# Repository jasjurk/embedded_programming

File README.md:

# embedded_programming
Some small projects for my electronics hobby.

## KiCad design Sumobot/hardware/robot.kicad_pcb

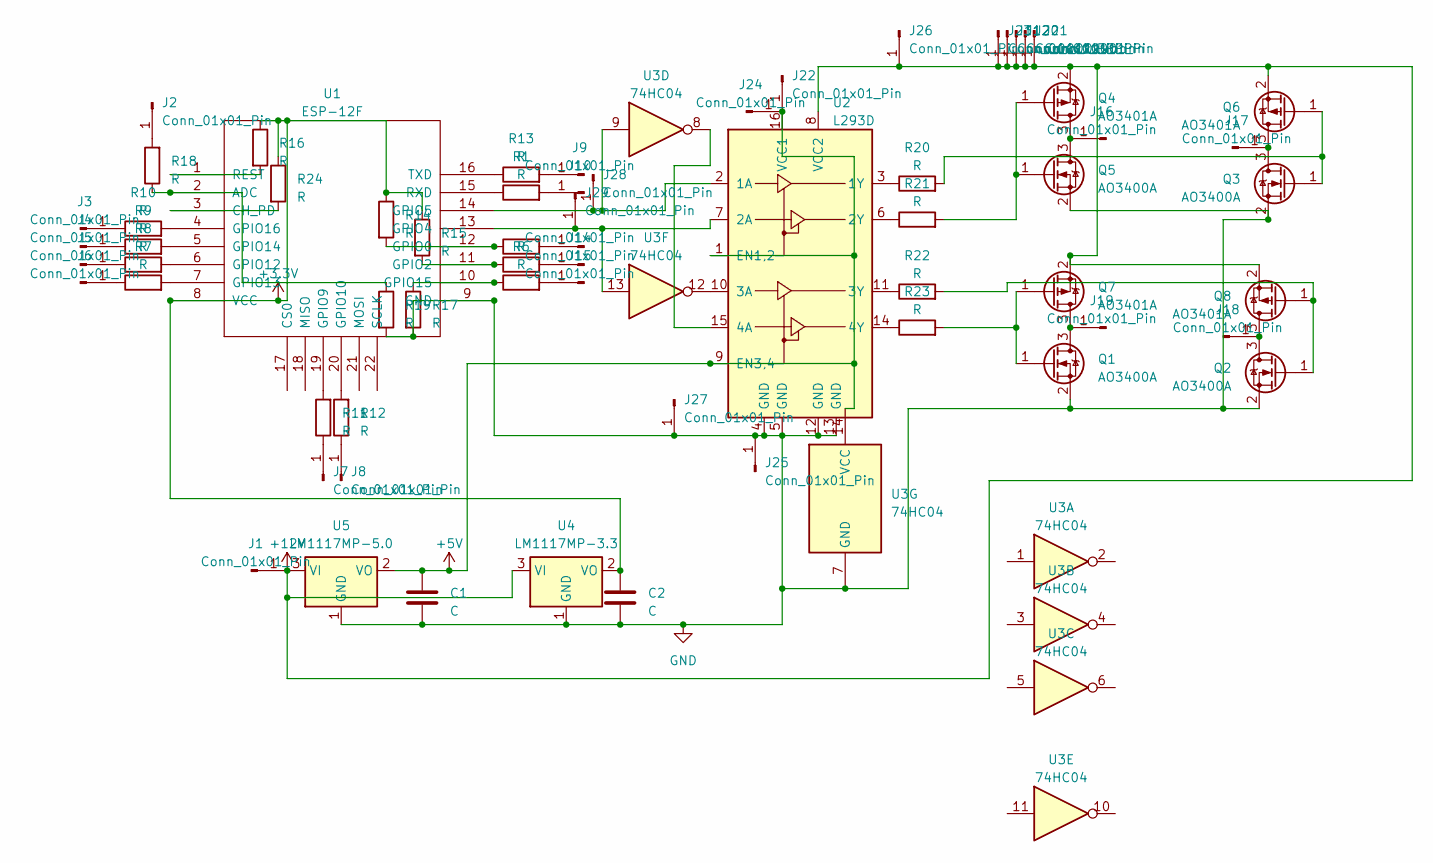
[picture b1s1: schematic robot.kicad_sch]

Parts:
C1, C2: C; C_1206_3216Metric_Pad1.33x1.80mm_HandSolder
J1, J2, J3, J4, J5, J6, J7, J8, J9, J10, J13, J14, J15, J16, J17, J18, J19, J25: Conn_01x01_Pin; SolderWirePad_1x01_SMD_1x2mm
J11, J12, J20, J21, J22, J23, J24, J26, J27, J28, J29: Conn_01x01_Pin; PinHeader_1x01_P1.00mm_Vertical
Q1, Q2, Q3, Q5: AO3400A; SOT-23
Q4, Q6, Q7, Q8: AO3401A; SOT-23
R1, R4, R5, R6, R7, R8, R9, R10, R11, R12, R13, R14, R15, R16, R17, R18, R19, R20, R21, R22, R23, R24: R; R_0805_2012Metric_Pad1.20x1.40mm_HandSolder
U1: ESP-12F; ESP-12E_SMD
U2: L293D; DIP-16_W7.62mm
U3: 74HC04; DIP-14_W7.62mm
U4: LM1117MP-3.3; SOT-223-3_TabPin2
U5: LM1117MP-5.0; SOT-223-3_TabPin2

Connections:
+3.3V: C2.1, R14.1, R15.1, R16.1, R24.1, U1.8 (VCC), U4.2 (VO)
+5V: C1.1, J22.1, J24.1, U2.1 (EN1,2), U2.9 (EN3,4), U2.16 (VCC1), U3.14 (VCC), U5.2 (VO)
+12V: J1.1, J11.1, J12.1, J20.1, J21.1, J23.1, J26.1, Q4.2 (S), Q6.2 (S), Q7.2 (S), Q8.2 (S), U2.8 (VCC2), U4.3 (VI), U5.3 (VI)
GND: C1.2, C2.2, J25.1, J27.1, Q1.2 (S), Q2.2 (S), Q3.2 (S), Q5.2 (S), R17.2, R19.2, U1.9 (GND), U2.4 (GND), U2.5 (GND), U2.12 (GND), U2.13 (GND), U3.7 (GND), U4.1 (GND), U5.1 (GND)
unnamed: J2.1, R18.2
unnamed: J3.1, R10.1
unnamed: J4.1, R9.1
unnamed: J5.1, R8.1
unnamed: J6.1, R7.1
unnamed: J7.1, R11.1
unnamed: J8.1, R12.1
unnamed: J9.1, R13.2
unnamed: J10.1, R1.2
unnamed: J13.1, R4.2
unnamed: J14.1, R5.2
unnamed: J15.1, R6.2
unnamed: J16.1, Q4.3 (D), Q5.3 (D)
unnamed: J17.1, Q3.3 (D), Q6.3 (D)
unnamed: J18.1, Q2.3 (D), Q8.3 (D)
unnamed: J19.1, Q1.3 (D), Q7.3 (D)
unnamed: J28.1, U1.14 (GPIO5), U2.2 (1A), U3.9
unnamed: J29.1, U1.13 (GPIO4), U2.7 (2A), U3.13
unnamed: Q1.1 (G), Q7.1 (G), R23.2
unnamed: Q2.1 (G), Q8.1 (G), R22.2
unnamed: Q3.1 (G), Q6.1 (G), R20.2
unnamed: Q4.1 (G), Q5.1 (G), R21.2
unnamed: R18.1, R19.1, U1.2 (ADC)
unnamed: R24.2, U1.3 (CH_PD)
unnamed: R4.1, R14.2, U1.12 (GPIO0)
unnamed: R5.1, R15.2, U1.11 (GPIO2)
unnamed: R11.2, U1.19 (GPIO9)
unnamed: R12.2, U1.20 (GPIO10)
unnamed: R8.2, U1.6 (GPIO12)
unnamed: R7.2, U1.7 (GPIO13)
unnamed: R9.2, U1.5 (GPIO14)
unnamed: R6.1, R17.1, U1.10 (GPIO15)
unnamed: R10.2, U1.4 (GPIO16)
unnamed: R16.2, U1.1 (REST)
unnamed: R1.1, U1.15 (RXD)
unnamed: R13.1, U1.16 (TXD)
unnamed: R20.1, U2.3 (1Y)
unnamed: R21.1, U2.6 (2Y)
unnamed: U2.10 (3A), U3.12
unnamed: R22.1, U2.11 (3Y)
unnamed: U2.15 (4A), U3.8
unnamed: R23.1, U2.14 (4Y)

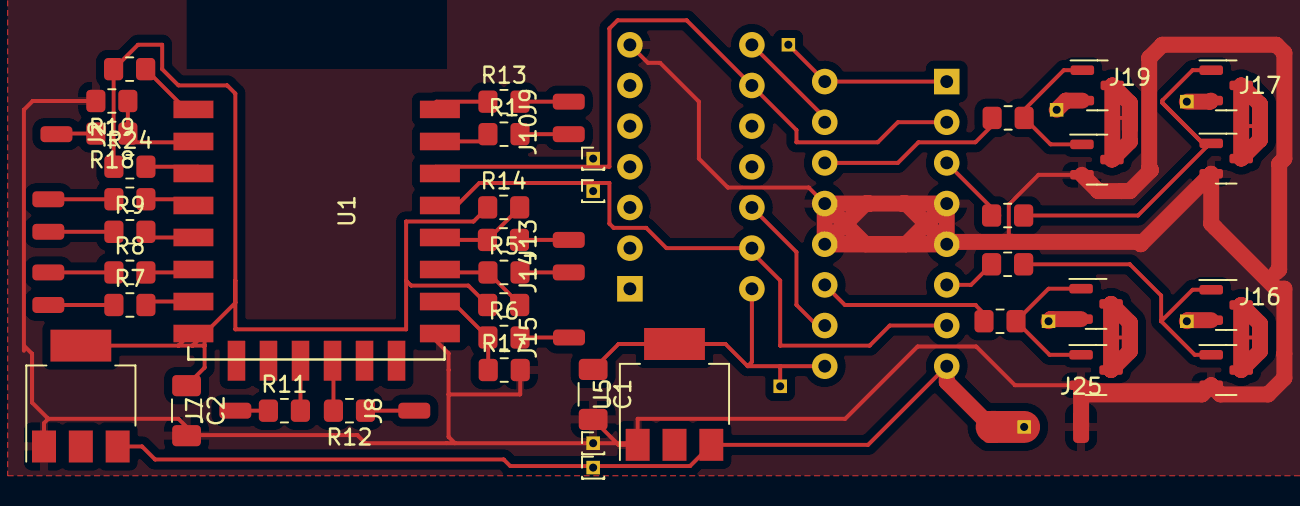
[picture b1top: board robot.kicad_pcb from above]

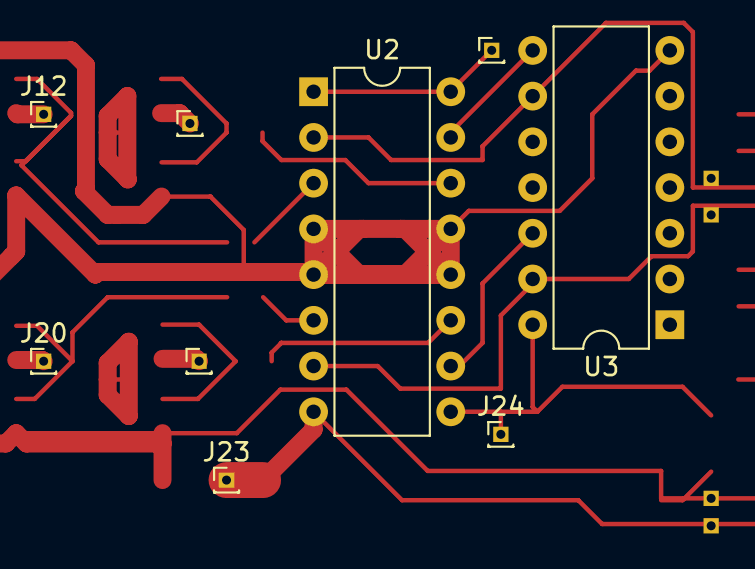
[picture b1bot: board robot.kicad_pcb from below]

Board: 2 copper layers, 66 parts (9 on the bottom side), 46 nets.

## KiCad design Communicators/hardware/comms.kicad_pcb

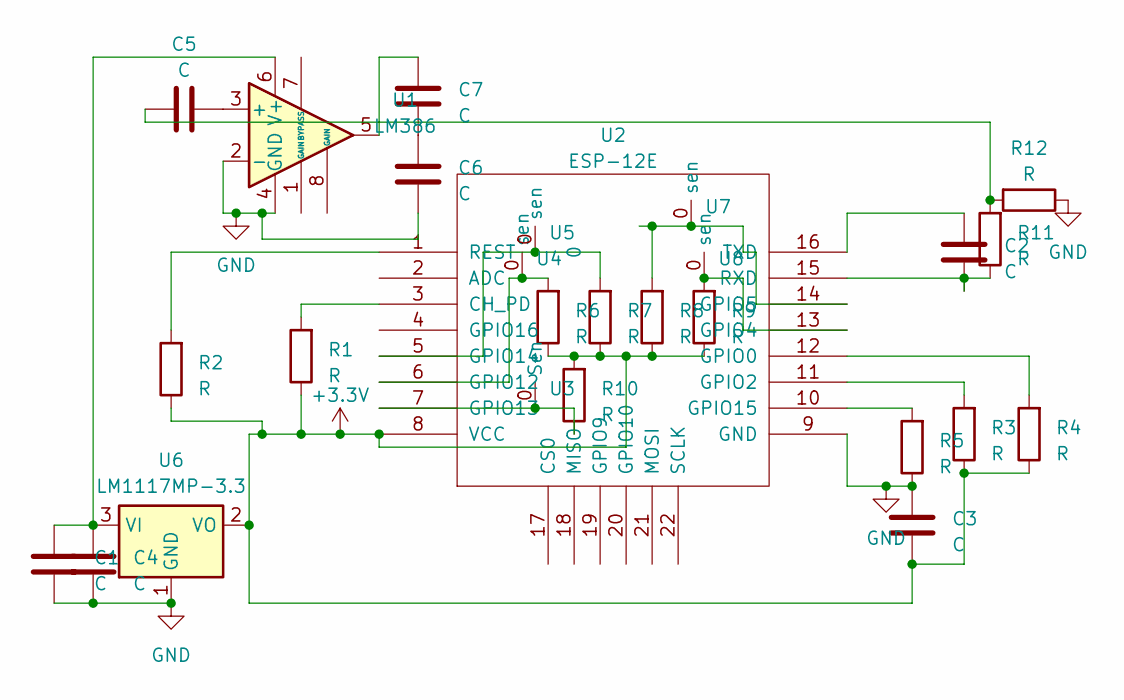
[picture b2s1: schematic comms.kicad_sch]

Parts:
C1, C2, C3, C4, C5, C6, C7: C; C_1206_3216Metric_Pad1.33x1.80mm_HandSolder
R1, R2, R3, R4, R5, R6, R7, R8, R9, R10, R11, R12: R; R_0805_2012Metric_Pad1.20x1.40mm_HandSolder
U1: LM386; SOIC-8_3.9x4.9mm_P1.27mm
U2: ESP-12E; ESP-12E_SMD
U3: cap_sensor
U4, U7, U8: circle
U5: 0; circle
U6: LM1117MP-3.3; SOT-223-3_TabPin2

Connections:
+3.3V: C3.2, R1.1, R2.1, R3.1, R4.1, R6.1, R7.1, R8.1, R9.1, R10.2, U2.8 (VCC), U6.2 (VO)
GND: C1.2, C3.1, C4.2, C6.2, R5.1, R12.1, U1.2 (-), U1.4 (GND), U2.9 (GND), U6.1 (GND)
unnamed: C5.1, R11.2, R12.2
unnamed: C6.1, C7.2
unnamed: C7.1, U1.5
unnamed: C5.2, U1.3 (+)
unnamed: C1.1, C4.1, U1.6 (V+), U6.3 (VI)
unnamed: R1.2, U2.3 (CH_PD)
unnamed: R4.2, U2.12 (GPIO0)
unnamed: R3.2, U2.11 (GPIO2)
unnamed: R9.2, U2.13 (GPIO4), U8.0 (sen)
unnamed: R8.2, U2.14 (GPIO5), U7.0 (sen)
unnamed: R6.2, U2.6 (GPIO12), U4.0 (sen)
unnamed: R10.1, U2.7 (GPIO13), U3.0 (Sen)
unnamed: R7.2, U2.5 (GPIO14), U5.0 (sen)
unnamed: R5.2, U2.10 (GPIO15)
unnamed: R2.2, U2.1 (REST)
unnamed: C2.2, R11.1, U2.15 (RXD)
unnamed: C2.1, U2.16 (TXD)

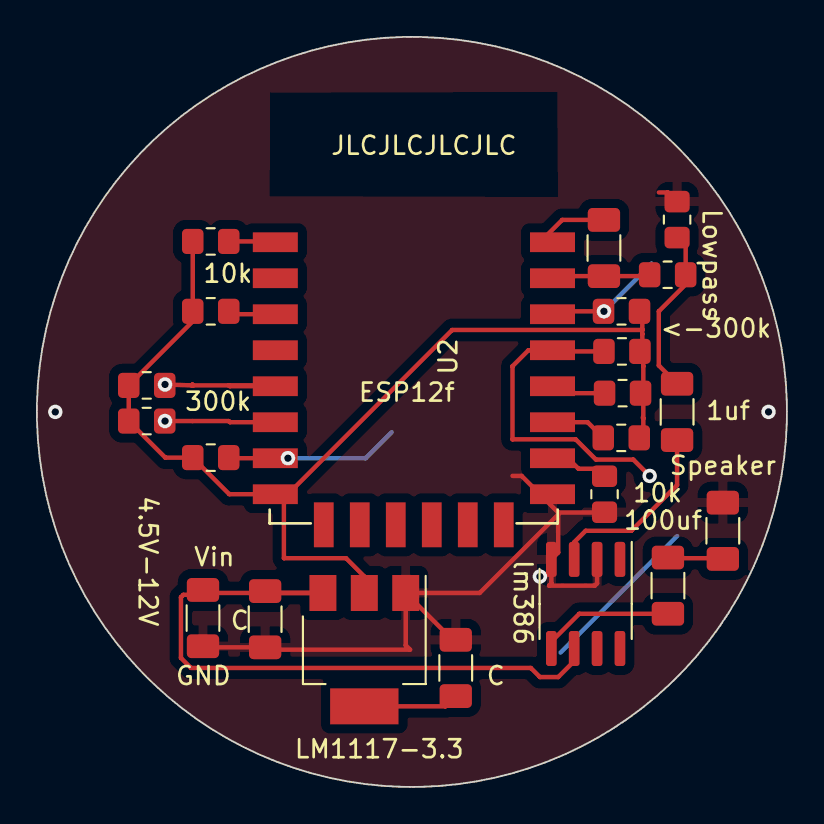
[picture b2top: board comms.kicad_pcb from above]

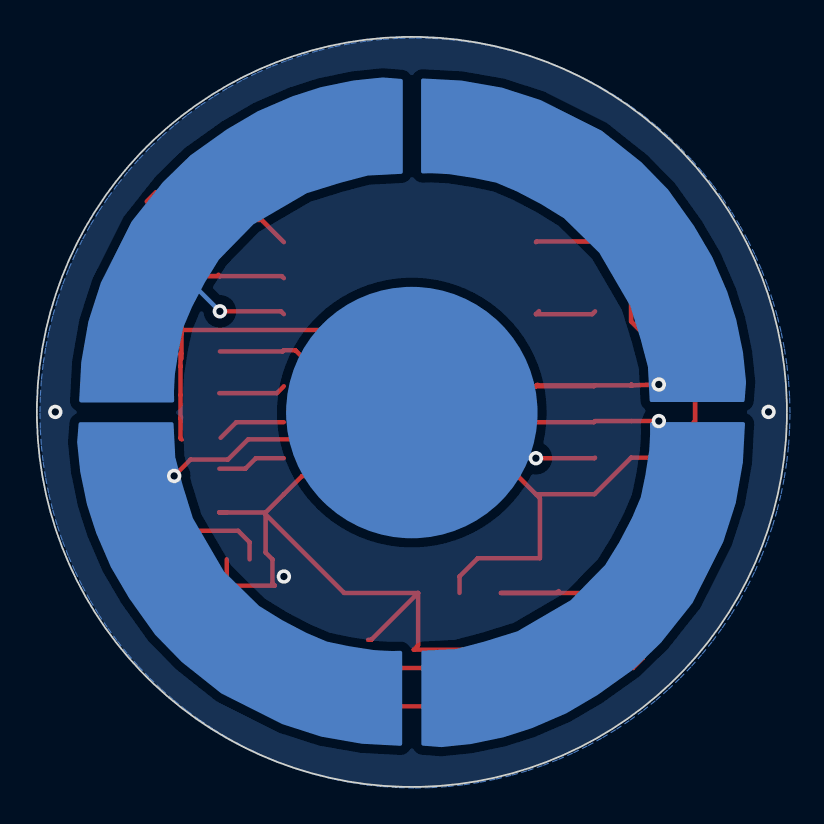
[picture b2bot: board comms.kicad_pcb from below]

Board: 2 copper layers, 41.7 x 41.7 mm, 27 parts (5 on the bottom side), 19 nets.

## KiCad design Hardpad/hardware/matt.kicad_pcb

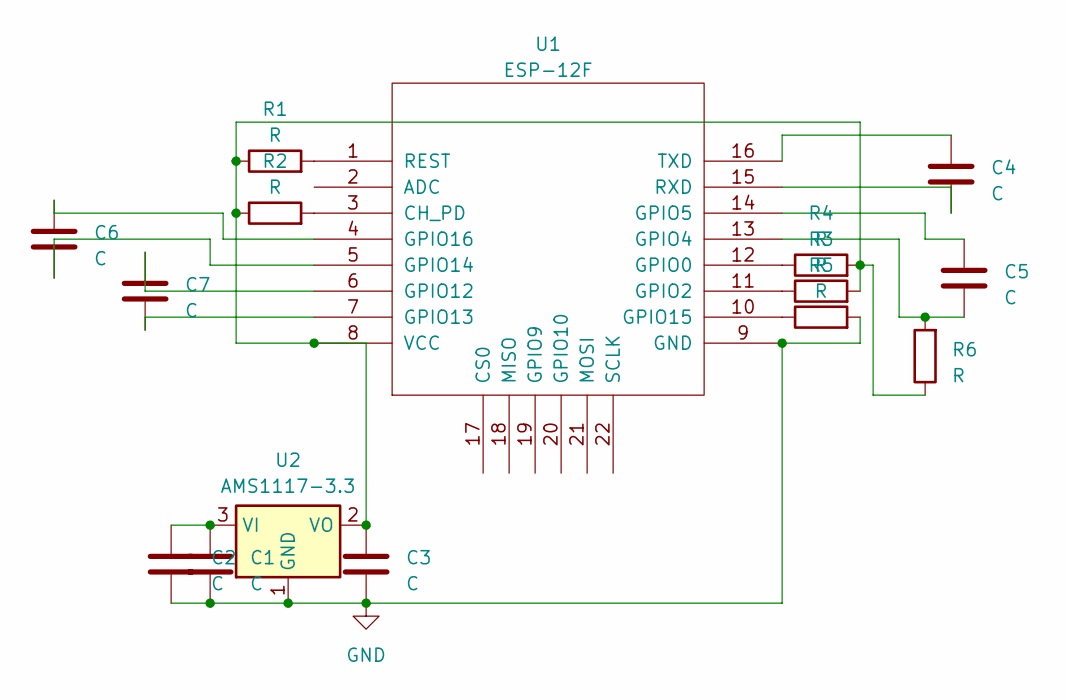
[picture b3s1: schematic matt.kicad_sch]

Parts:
C1, C2, C3, C4, C5, C6, C7: C; C_1206_3216Metric_Pad1.33x1.80mm_HandSolder
R1, R2, R3, R4, R5, R6: R; R_0805_2012Metric_Pad1.20x1.40mm_HandSolder
U1: ESP-12F; ESP-12E_SMD
U2: AMS1117-3.3; SOT-223-3_TabPin2

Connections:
GND: C1.2, C2.2, C3.2, R5.2, U1.9 (GND), U2.1 (GND)
unnamed: R2.2, U1.3 (CH_PD)
unnamed: R4.1, U1.12 (GPIO0)
unnamed: R3.1, U1.11 (GPIO2)
unnamed: C5.2, R6.2, U1.13 (GPIO4)
unnamed: C5.1, U1.14 (GPIO5)
unnamed: C7.1, U1.6 (GPIO12)
unnamed: C7.2, U1.7 (GPIO13)
unnamed: C6.2, U1.5 (GPIO14)
unnamed: R5.1, U1.10 (GPIO15)
unnamed: C6.1, U1.4 (GPIO16)
unnamed: R1.2, U1.1 (REST)
unnamed: C4.2, U1.15 (RXD)
unnamed: C4.1, U1.16 (TXD)
unnamed: C3.1, R1.1, R2.1, R3.2, R4.2, R6.1, U1.8 (VCC), U2.2 (VO)
unnamed: C1.1, C2.1, U2.3 (VI)

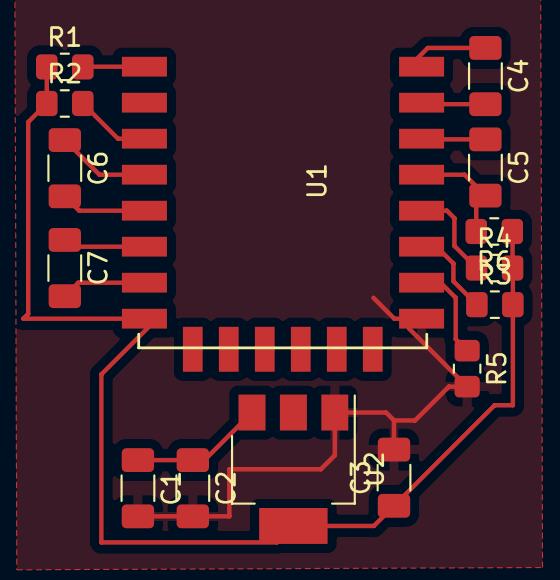
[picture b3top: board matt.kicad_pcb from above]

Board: 2 copper layers, 15 parts (0 on the bottom side), 16 nets.

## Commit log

2023-10-23 Blanket addition of many smaller projects, especially Audio objects, mostly written in arduino
2023-10-23 Added readme's
2023-10-28 added submodule of source for hardpad
